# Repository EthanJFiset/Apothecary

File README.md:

# Apothecary
Apothocary is an STM32H7-based USB audio interface and DSP board designed for prototyping real-time guitar effects. Features include a robust STM32H7 MCU complete with external SDRAM and QPSI flash memory, 24-bit 144-dB stereo codec, USB 2.0 connectivity and expansion ports for an external stomp box.

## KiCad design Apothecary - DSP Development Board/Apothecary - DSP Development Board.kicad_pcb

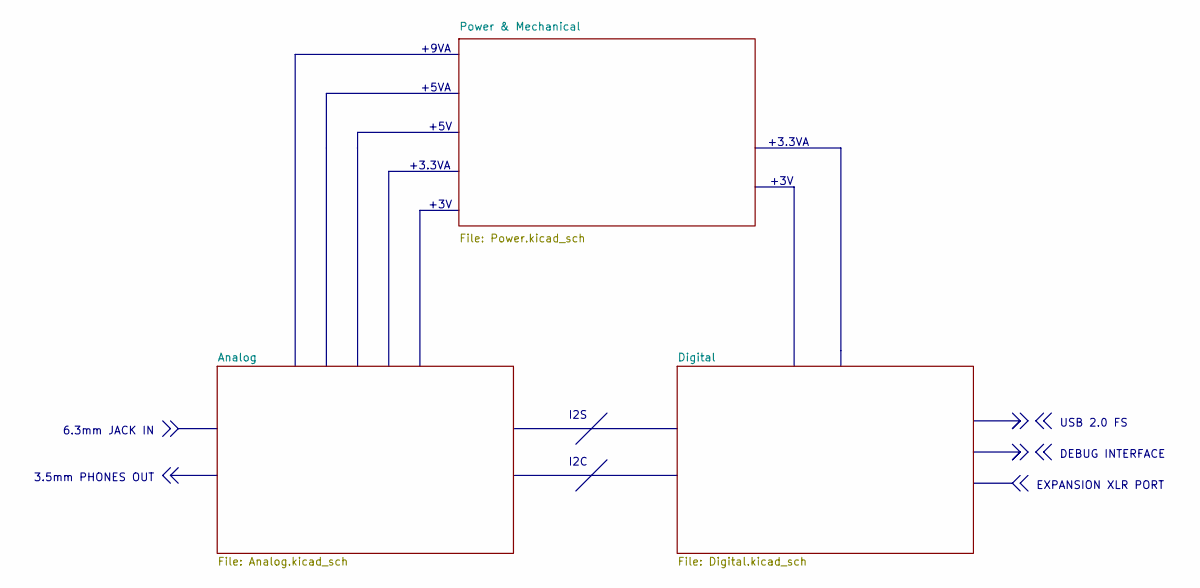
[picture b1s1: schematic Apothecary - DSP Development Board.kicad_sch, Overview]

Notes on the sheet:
+9VA
+3V
EXPANSION XLR PORT
6.3mm JACK IN
DEBUG INTERFACE
USB 2.0 FS
+5V
I2C
+3.3VA
3.5mm PHONES OUT
+5VA
I2S

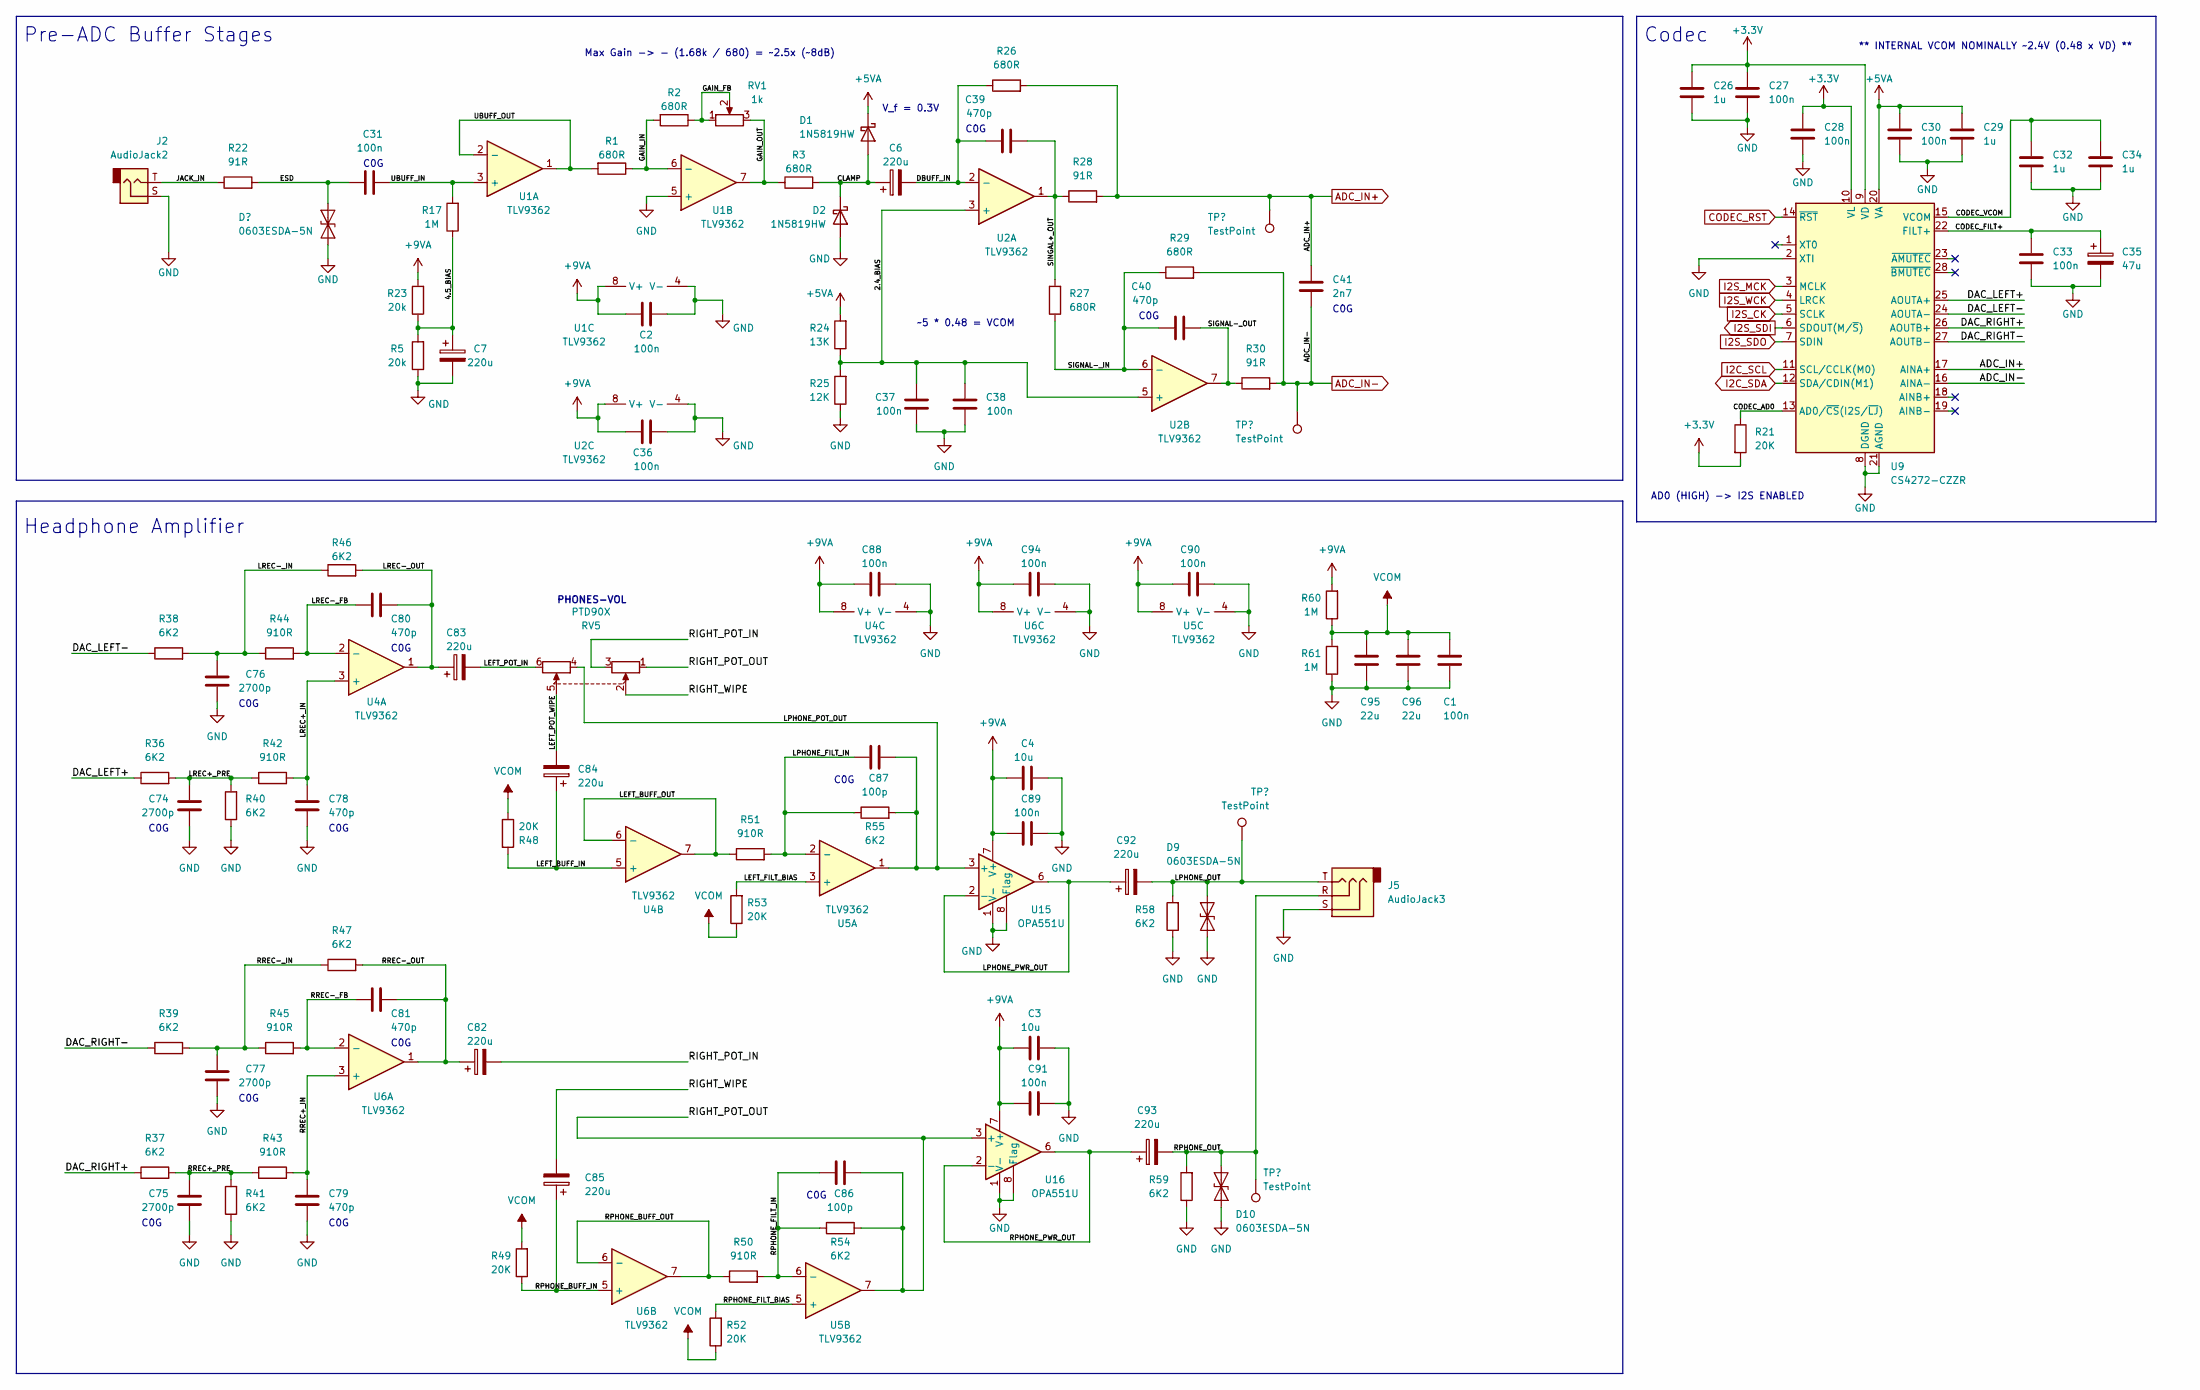
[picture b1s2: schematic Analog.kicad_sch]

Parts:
C1, C2, C27, C28, C30, C31, C33, C36, C37, C38, C88, C89, C90, C91, C94: 100n; C_0402_1005Metric
C3, C4: 10u; C_0805_2012Metric
C6, C7, C82, C83, C84, C85, C92, C93: 220u; CP_Elec_6.3x7.7
C26, C29, C32, C34: 1u; C_0402_1005Metric
C35: 47u; CP_Elec_6.3x7.7
C39, C40, C78, C79, C80, C81: 470p; C_0402_1005Metric
C41: 2n7; C_0603_1608Metric
C74, C75, C76, C77: 2700p; C_0603_1608Metric
C86, C87: 100p; C_0402_1005Metric
C95, C96: 22u; C_1210_3225Metric
D1, D2: 1N5819HW; D_SOD-123
D8, D9, D10: 0603ESDA-5N; D_0603_1608Metric
J2: AudioJack2; Jack_6.35mm_Neutrik_NMJ4HCD2_Horizontal
J5: AudioJack3; Jack_3.5mm_CUI_SJ1-3533NG_Horizontal
R1, R2, R3, R26, R27, R29: 680R; R_0603_1608Metric
R5, R23: 20k; R_0603_1608Metric
R17, R60, R61: 1M; R_0805_2012Metric
R21, R48, R49, R52, R53: 20K; R_0603_1608Metric
R22, R28, R30: 91R; R_0603_1608Metric
R24: 13K; R_0603_1608Metric
R25: 12K; R_0603_1608Metric
R36, R37, R38, R39, R40, R41, R46, R47, R54, R55, R58, R59: 6K2; R_0603_1608Metric
R42, R43, R44, R45, R50, R51: 910R; R_0603_1608Metric
RV1: 1k; Potentiometer_Bourns_PTV09A-2_Single_Horizontal
RV5: PTD90X; PTD-902
TP11, TP12, TP13, TP14: TestPoint; TestPoint_Pad_D1.0mm
U1, U2, U4, U5, U6: TLV9362; SOIC-8-1EP_3.9x4.9mm_P1.27mm_EP2.41x3.81mm
U9: CS4272-CZZR; TSSOP-28_4.4x9.7mm_P0.65mm
U15, U16: OPA551U; SOIC-8_3.9x4.9mm_P1.27mm

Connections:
+3.3V: C26.1, C27.1, C28.1, R21.2, U9.9 (VD), U9.10 (VL); also elsewhere on the board
+5VA: C29.1, C30.1, D1.1 (K), R24.2, U9.20 (VA); also elsewhere on the board
+9VA: C2.1, C3.2, C4.2, C36.1, C88.2, C89.2, C90.2, C91.2, C94.2, R23.2, R60.2, U1.8 (V+), U2.8 (V+), U4.8 (V+), U5.8 (V+), U6.8 (V+), U15.7 (V+), U16.7 (V+); also elsewhere on the board
/Analog/2.4_BIAS: C37.2, C38.2, R24.1, R25.2, U2.3 (+), U2.5 (+)
/Analog/4.5_BIAS: C7.1, R5.2, R17.1, R23.1
/Analog/CLAMP: C6.1, D1.2 (A), D2.1 (K), R3.2
/Analog/CODEC_AD0: R21.1, U9.13 (AD0/~CS(I2S/~LJ))
/Analog/CODEC_FILT+: C33.1, C35.1, U9.22 (FILT+)
/Analog/CODEC_VCOM: C32.1, C34.1, U9.15 (VCOM)
/Analog/DAC_LEFT+: R36.1, U9.25 (AOUTA+)
/Analog/DAC_LEFT-: R38.1, U9.24 (AOUTA-)
/Analog/DAC_RIGHT+: R37.1, U9.26 (AOUTB+)
/Analog/DAC_RIGHT-: R39.1, U9.27 (AOUTB-)
/Analog/DBUFF_IN: C6.2, C39.1, R26.1, U2.2 (-)
/Analog/ESD: C31.1, D8.2 (A2), R22.2
/Analog/GAIN_FB: R2.1, RV1.1, RV1.2
/Analog/GAIN_IN: R1.1, R2.2, U1.6 (-)
/Analog/GAIN_OUT: R3.1, RV1.3, U1.7
/Analog/JACK_IN: J2.T, R22.1
/Analog/LEFT_BUFF_IN: C84.1, R48.2, U4.5 (+)
/Analog/LEFT_BUFF_OUT: R51.1, U4.6 (-), U4.7
/Analog/LEFT_FILT_BIAS: R53.2, U5.3 (+)
/Analog/LEFT_POT_IN: C83.2, RV5.6
/Analog/LEFT_POT_WIPE: C84.2, RV5.5
/Analog/LPHONE_FILT_IN: C87.2, R51.2, R55.1, U5.2 (-)
/Analog/LPHONE_OUT: C92.2, D9.2 (A2), J5.T, R58.2, TP13.1
/Analog/LPHONE_POT_OUT: C87.1, R55.2, RV5.4, U5.1, U15.3 (+)
/Analog/LPHONE_PWR_OUT: C92.1, U15.2 (-), U15.6
/Analog/LREC+_IN: C78.1, R42.2, U4.3 (+)
/Analog/LREC+_PRE: C74.1, R36.2, R40.2, R42.1
/Analog/LREC-_FB: C80.2, R44.2, U4.2 (-)
/Analog/LREC-_IN: C76.1, R38.2, R44.1, R46.1
/Analog/LREC-_OUT: C80.1, C83.1, R46.2, U4.1
/Analog/RIGHT_POT_IN: C82.2, RV5.3
/Analog/RIGHT_POT_OUT: C86.1, R54.2, RV5.1, U5.7, U16.3 (+)
/Analog/RIGHT_WIPE: C85.2, RV5.2
/Analog/RPHONE_BUFF_IN: C85.1, R49.1, U6.5 (+)
/Analog/RPHONE_BUFF_OUT: R50.1, U6.6 (-), U6.7
/Analog/RPHONE_FILT_BIAS: R52.2, U5.5 (+)
/Analog/RPHONE_FILT_IN: C86.2, R50.2, R54.1, U5.6 (-)
/Analog/RPHONE_OUT: C93.2, D10.2 (A2), J5.R, R59.2, TP14.1
/Analog/RPHONE_PWR_OUT: C93.1, U16.2 (-), U16.6
/Analog/RREC+_IN: C79.1, R43.2, U6.3 (+)
/Analog/RREC+_PRE: C75.1, R37.2, R41.2, R43.1
/Analog/RREC-_FB: C81.2, R45.2, U6.2 (-)
/Analog/RREC-_IN: C77.1, R39.2, R45.1, R47.1
/Analog/RREC-_OUT: C81.1, C82.1, R47.2, U6.1
/Analog/SIGNAL-_IN: C40.1, R27.1, R29.1, U2.6 (-)
/Analog/SIGNAL-_OUT: C40.2, R30.1, U2.7
/Analog/SINGAL+_OUT: C39.2, R27.2, R28.1, U2.1
/Analog/UBUFF_IN: C31.2, R17.2, U1.3 (+)
/Analog/UBUFF_OUT: R1.2, U1.1, U1.2 (-)
ADC_IN+: C41.1, R26.2, R28.2, TP12.1, U9.17 (AINA+)
ADC_IN-: C41.2, R29.2, R30.2, TP11.1, U9.16 (AINA-)
CODEC_RST: U9.14 (~RST); also elsewhere on the board
GND: C1.2, C2.2, C3.1, C4.1, C7.2, C26.2, C27.2, C28.2, C29.2, C30.2, C32.2, C33.2, C34.2, C35.2, C36.2, C37.1, C38.1, C74.2, C75.2, C76.2, C77.2, C78.2, C79.2, C88.1, C89.1, C90.1, C91.1, C94.1, C95.2, C96.2, D2.2 (A), D8.1 (A1), D9.1 (A1), D10.1 (A1), J2.S, J5.S, R5.1, R25.1, R40.1, R41.1, R58.1, R59.1, R61.1, U1.4 (V-), U1.5 (+), U2.4 (V-), U4.4 (V-), U5.4 (V-), U6.4 (V-), U9.2 (XTI), U9.8 (DGND), U9.21 (AGND), U15.1 (V-), U15.4 (V-), U15.5 (V-), U15.8 (Flag), U16.1 (V-), U16.4 (V-), U16.5 (V-), U16.8 (Flag); also elsewhere on the board
I2C_SCL: U9.11 (SCL/CCLK(M0)); also elsewhere on the board
I2C_SDA: U9.12 (SDA/CDIN(M1)); also elsewhere on the board
I2S_CK: U9.5 (SCLK); also elsewhere on the board
I2S_MCK: U9.3 (MCLK); also elsewhere on the board
I2S_SDI: U9.6 (SDOUT(M/~S)); also elsewhere on the board
I2S_SDO: U9.7 (SDIN); also elsewhere on the board
I2S_WCK: U9.4 (LRCK); also elsewhere on the board
VCOM: C1.1, C95.1, C96.1, R48.1, R49.2, R52.1, R53.1, R60.1, R61.2

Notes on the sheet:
C0G
Pre-ADC Buffer Stages
** INTERNAL VCOM NOMINALLY ~2.4V (0.48 x VD) **
Headphone Amplifier
V_f = 0.3V
PHONES-VOL
Codec
~5 * 0.48 = VCOM
AD0 (HIGH) -> I2S ENABLED
Max Gain -> - (1.68k / 680) = ~2.5x (~8dB)

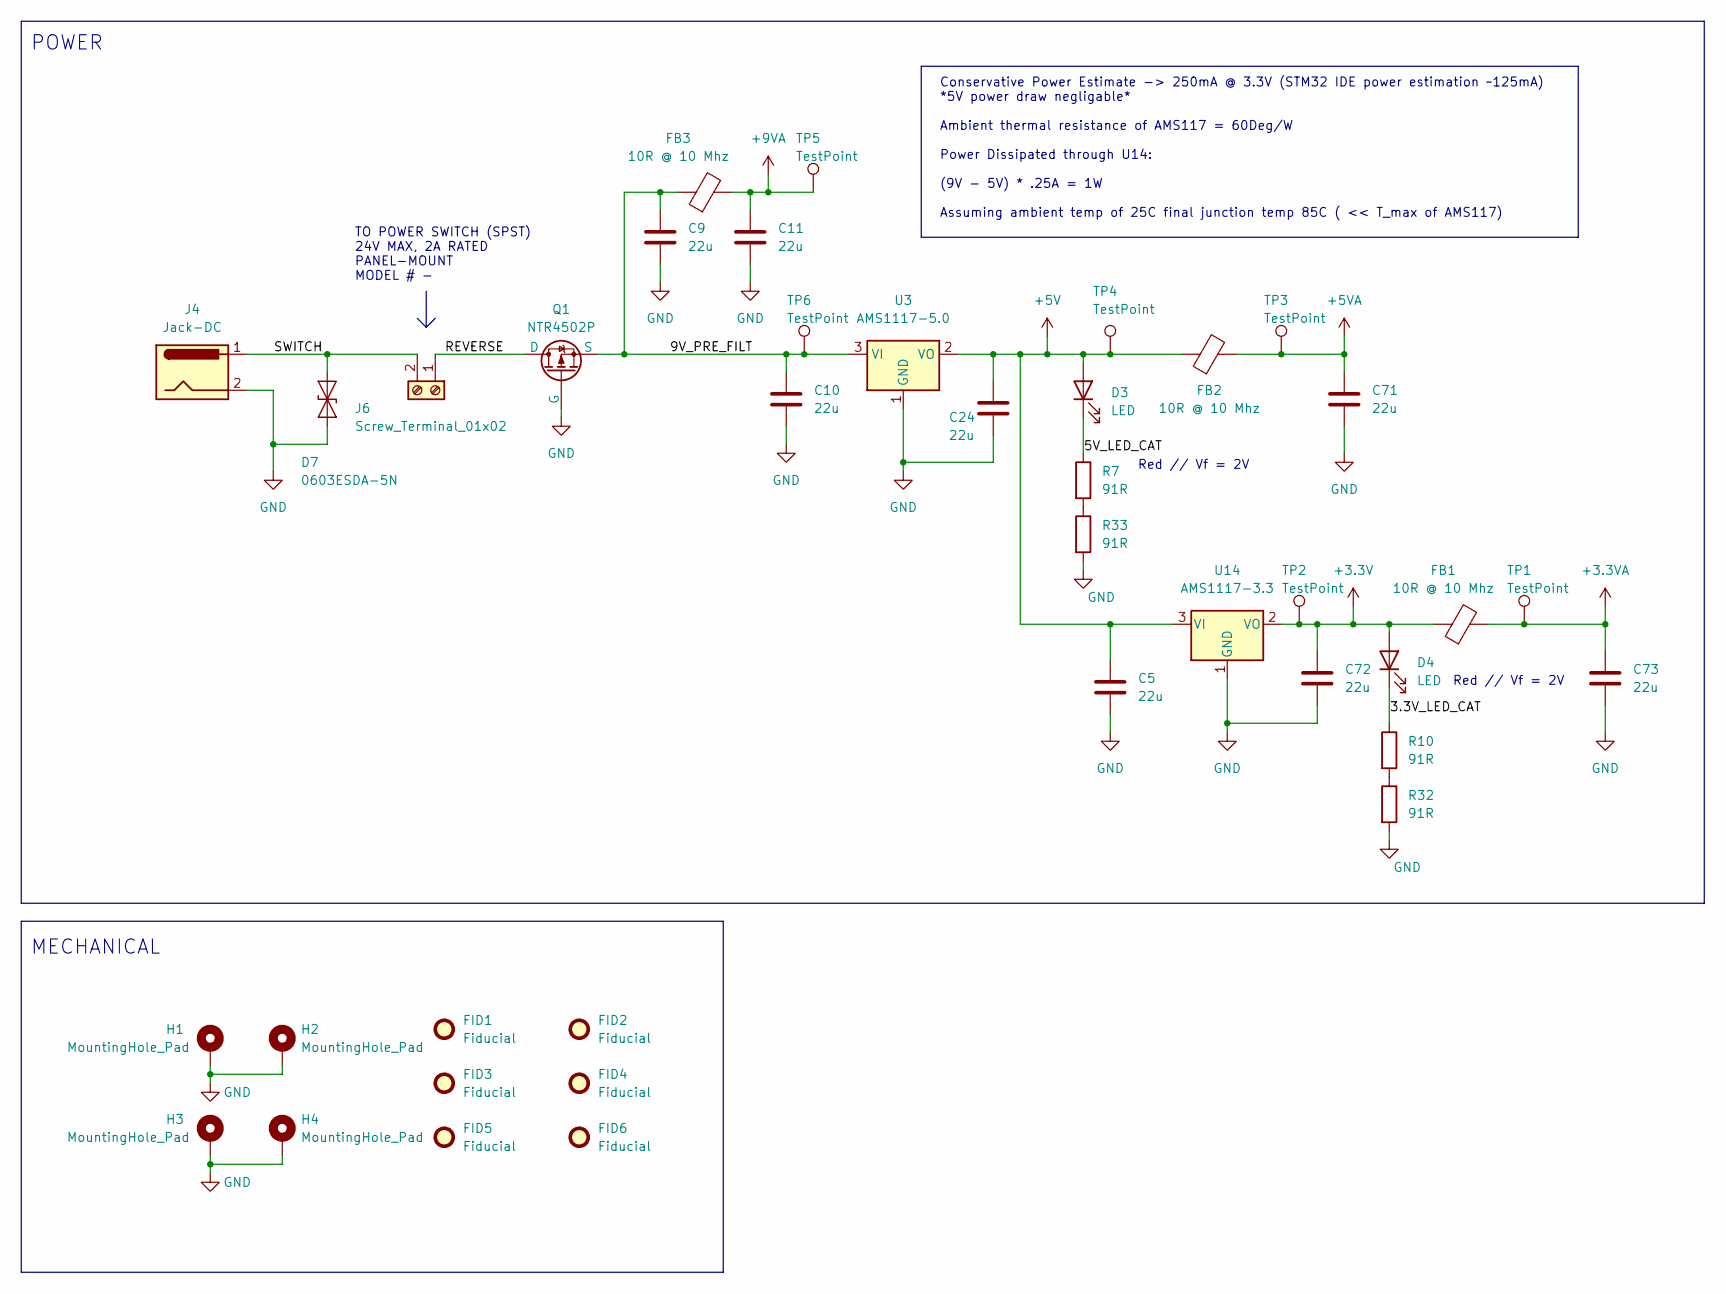
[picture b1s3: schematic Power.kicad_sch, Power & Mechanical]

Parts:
C5, C9, C10, C11, C24, C71, C72, C73: 22u; C_1210_3225Metric
D3, D4: LED; LED_0603_1608Metric
D7: 0603ESDA-5N; D_0603_1608Metric
FB1, FB2, FB3: 10R @ 10 Mhz; L_0805_2012Metric
FID1, FID2, FID3, FID4, FID5, FID6: Fiducial; Fiducial_0.5mm_Mask1mm
H1, H2, H3, H4: MountingHole_Pad; MountingHole_2.7mm_M2.5_DIN965_Pad
J4: Jack-DC; BarrelJack_CUI_PJ-063AH_Horizontal
J6: Screw_Terminal_01x02; TerminalBlock_Phoenix_MKDS-1,5-2_1x02_P5.00mm_Horizontal
Q1: NTR4502P; SOT-23
R7, R10, R32, R33: 91R; R_0603_1608Metric
TP1, TP2, TP3, TP4, TP5, TP6: TestPoint; TestPoint_Pad_D1.5mm
U3: AMS1117-5.0; SOT-223-3_TabPin2
U14: AMS1117-3.3; SOT-223-3_TabPin2

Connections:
+3.3V: C72.2, D4.2 (A), FB1.1, TP2.1, U14.2 (VO); also elsewhere on the board
+3.3VA: C73.2, FB1.2, TP1.1; also elsewhere on the board
+5V: C5.2, C24.2, D3.2 (A), FB2.1, TP4.1, U3.2 (VO), U14.3 (VI)
+5VA: C71.2, FB2.2, TP3.1; also elsewhere on the board
+9VA: C11.2, FB3.2, TP5.1; also elsewhere on the board
/Power & Mechanical/3.3V_LED_CAT: D4.1 (K), R10.1
/Power & Mechanical/5V_LED_CAT: D3.1 (K), R7.1
/Power & Mechanical/9V_PRE_FILT: C9.2, C10.2, FB3.1, Q1.3 (S), TP6.1, U3.3 (VI)
/Power & Mechanical/REVERSE: J6.1, Q1.1 (D)
/Power & Mechanical/SWITCH: D7.2 (A2), J4.1, J6.2
GND: C5.1, C9.1, C10.1, C11.1, C24.1, C71.1, C72.1, C73.1, D7.1 (A1), H1.1, H2.1, H3.1, H4.1, J4.2, Q1.2 (G), R32.2, R33.2, U3.1 (GND), U14.1 (GND); also elsewhere on the board
unnamed: R10.2, R32.1
unnamed: R7.2, R33.1

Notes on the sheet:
Conservative Power Estimate -> 250mA @ 3.3V (STM32 IDE power estimation ~125mA) *5V power draw negligable* Ambient thermal resistance of AMS117 = 60Deg/W Power Dissipated through U14: (9V - 5V) * .25A = 1W Assuming ambient temp of 25C final junction temp 85C ( << T_max of AMS117)
TO POWER SWITCH (SPST) 24V MAX, 2A RATED PANEL-MOUNT MODEL # -
MECHANICAL
POWER
Red // Vf = 2V

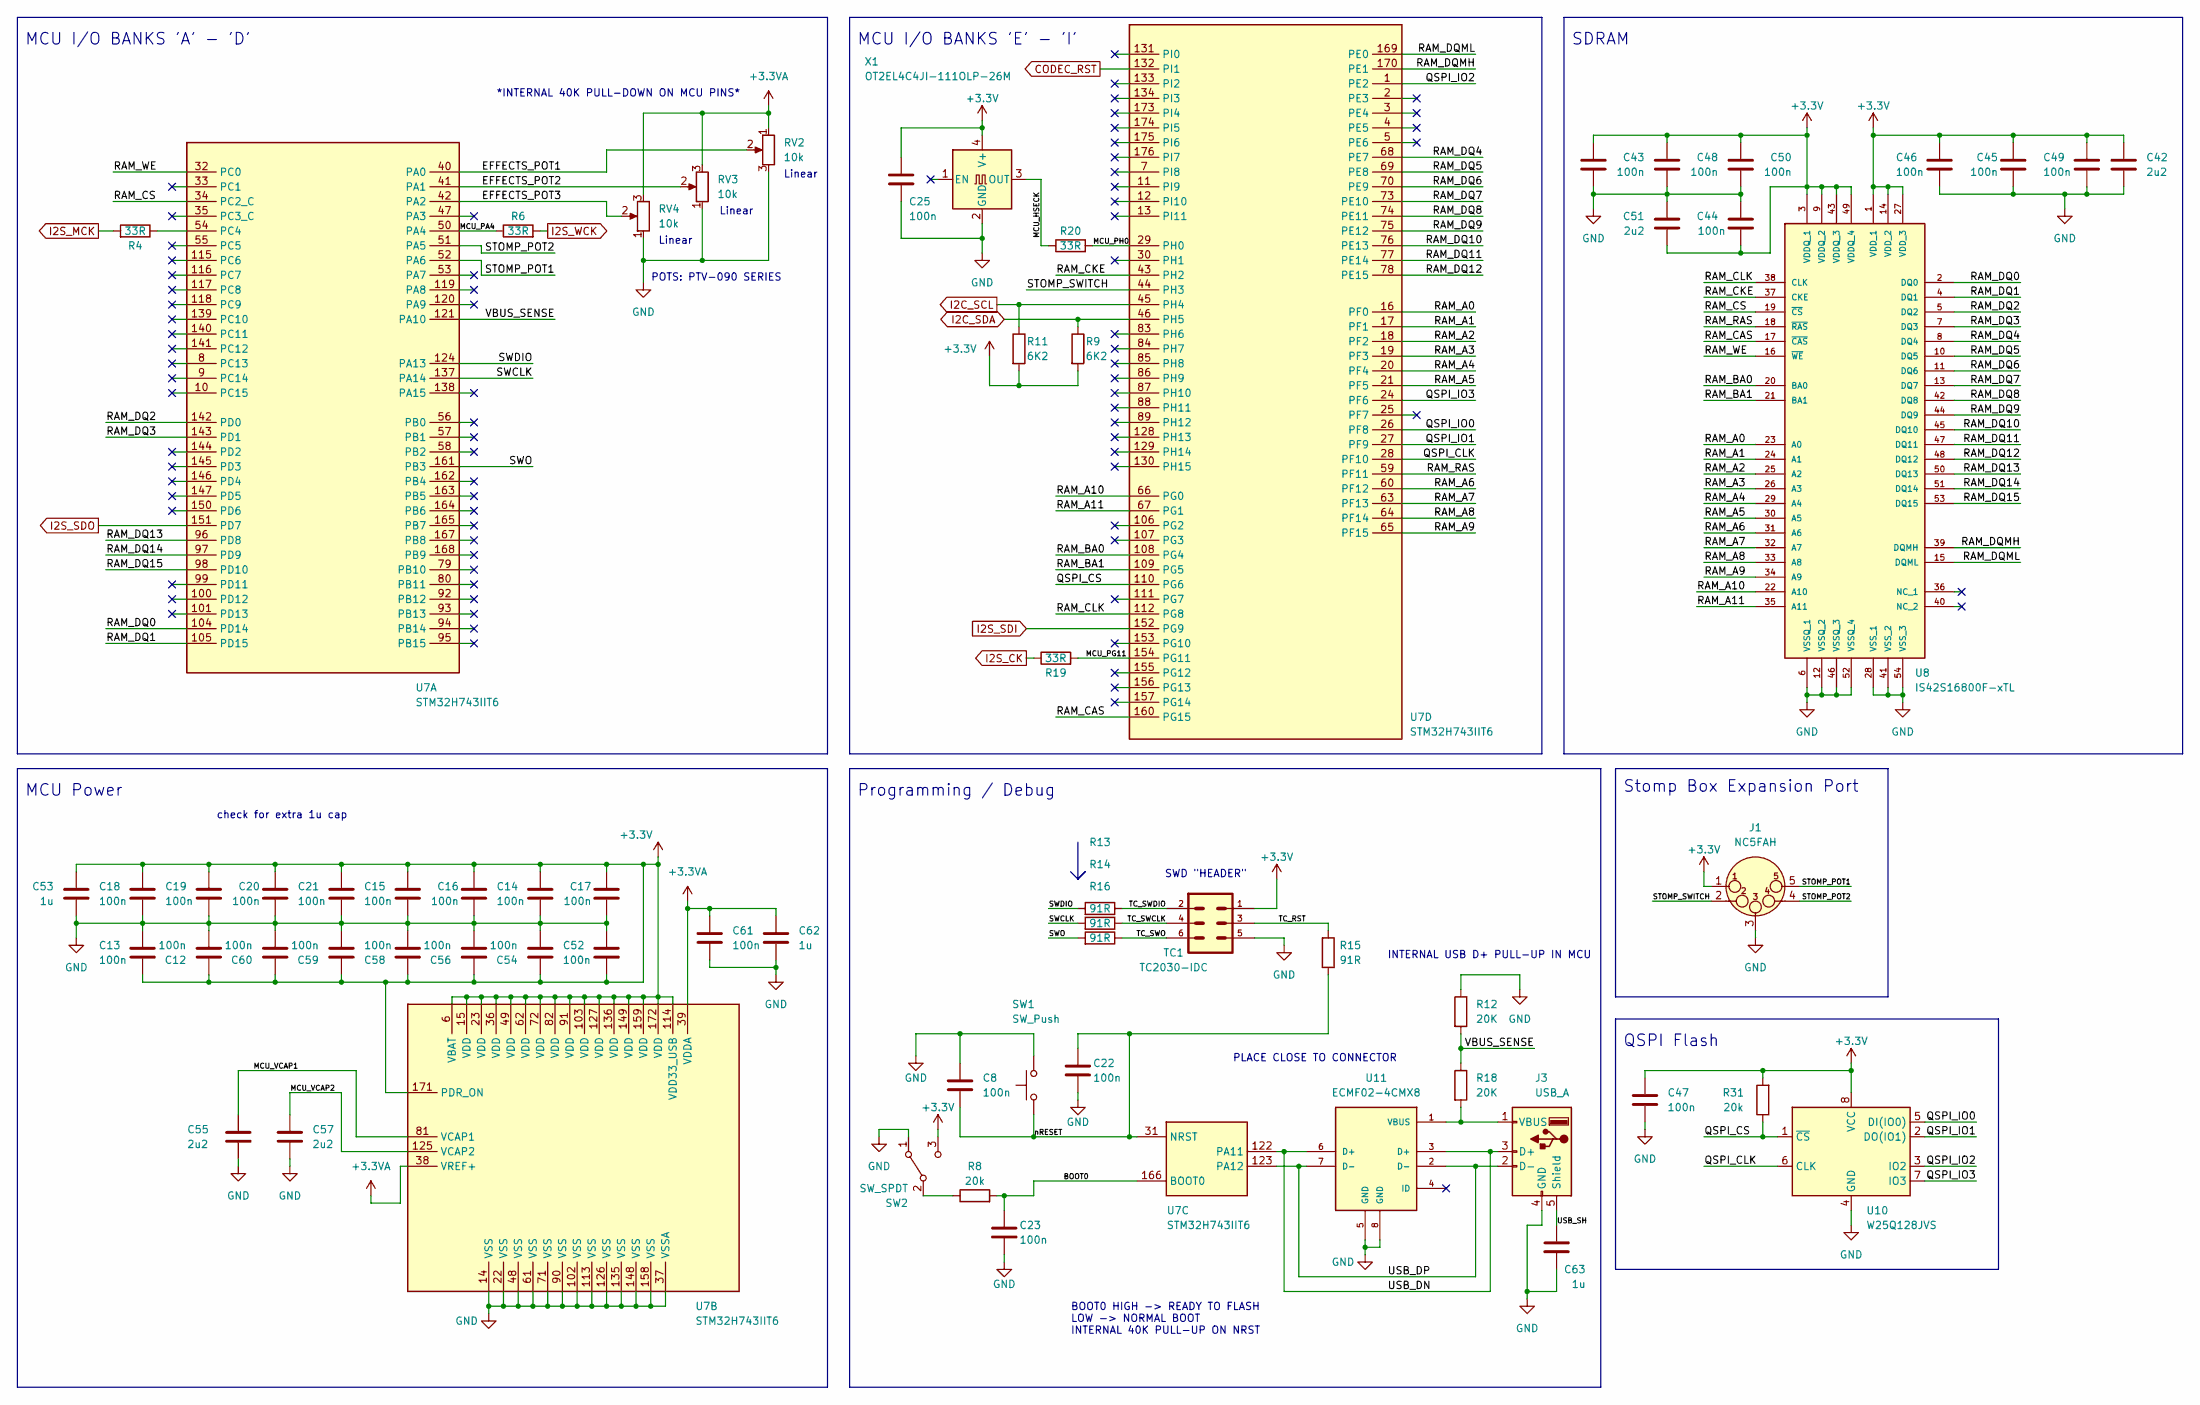
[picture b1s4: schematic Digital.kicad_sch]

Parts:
C8, C12, C13, C14, C15, C16, C17, C18, C19, C20, C21, C22, C23, C25, C43, C44, C45, C46, C47, C48, C49, C50, C52, C54, C56, C58, C59, C60, C61: 100n; C_0402_1005Metric
C42, C51, C55, C57: 2u2; C_0805_2012Metric
C53, C62, C63: 1u; C_0402_1005Metric
J1: NC5FAH; Jack_XLR_Neutrik_NC5FAH_Horizontal
J3: USB_A; MOLEX_0480372200
R4, R6, R19, R20: 33R; R_0603_1608Metric
R8, R31: 20k; R_0603_1608Metric
R9, R11: 6K2; R_0603_1608Metric
R12, R18: 20K; R_0603_1608Metric
R13, R14, R15, R16: 91R; R_0603_1608Metric
RV2, RV3, RV4: 10k; Potentiometer_Bourns_PTV09A-2_Single_Horizontal
SW1: SW_Push; Pushbutton_CUI_TS04
SW2: SW_SPDT; SW_E-Switch_EG1224_SPDT_Angled
TC1: TC2030-IDC; Tag-Connect_TC2030-IDC-FP_2x03_P1.27mm_Vertical
U7: STM32H743IIT6; LQFP-176_24x24mm_P0.5mm
U8: IS42S16800F-xTL; TSOP-II-54_22.2x10.16mm_P0.8mm; MOUSER_PART_NUMBER 870-IS42S16800F-7TL
U10: W25Q128JVS; SOIC-8_5.23x5.23mm_P1.27mm
U11: ECMF02-4CMX8; FIL_ECMF02-4CMX8; PARTREV 3
X1: OT2EL4C4JI-111OLP-26M; Crystal_SMD_3225-4Pin_3.2x2.5mm

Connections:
+3.3V: C12.1, C13.1, C14.2, C15.2, C16.2, C17.2, C18.2, C19.2, C20.2, C21.2, C25.1, C42.2, C43.2, C44.1, C45.2, C46.2, C47.1, C48.2, C49.2, C50.2, C51.1, C52.1, C53.2, C54.1, C56.1, C58.1, C59.1, C60.1, J1.1, R9.2, R11.2, R31.2, SW2.3 (C), TC1.1, U7.6 (VBAT), U7.15 (VDD), U7.23 (VDD), U7.36 (VDD), U7.49 (VDD), U7.62 (VDD), U7.72 (VDD), U7.82 (VDD), U7.91 (VDD), U7.103 (VDD), U7.114 (VDD33_USB), U7.127 (VDD), U7.136 (VDD), U7.149 (VDD), U7.159 (VDD), U7.171 (PDR_ON), U7.172 (VDD), U8.1 (VDD_1), U8.3 (VDDQ_1), U8.9 (VDDQ_2), U8.14 (VDD_2), U8.27 (VDD_3), U8.43 (VDDQ_3), U8.49 (VDDQ_4), U10.8 (VCC), X1.4 (V+); also elsewhere on the board
+3.3VA: C61.1, C62.1, RV2.1, RV3.3, RV4.3, U7.38 (VREF+), U7.39 (VDDA); also elsewhere on the board
/Digital/BOOT0: C23.1, R8.2, U7.166 (BOOT0)
/Digital/EFFECTS_POT1: RV2.2, U7.40 (PA0)
/Digital/EFFECTS_POT2: RV3.2, U7.41 (PA1)
/Digital/EFFECTS_POT3: RV4.2, U7.42 (PA2)
/Digital/MCU_HSECK: R20.1, X1.3 (OUT)
/Digital/MCU_PA4: R6.1, U7.50 (PA4)
/Digital/MCU_PG11: R19.2, U7.154 (PG11)
/Digital/MCU_PH0: R20.2, U7.29 (PH0)
/Digital/MCU_VCAP1: C55.1, U7.81 (VCAP1)
/Digital/MCU_VCAP2: C57.1, U7.125 (VCAP2)
/Digital/QSPI_CLK: U7.28 (PF10), U10.6 (CLK)
/Digital/QSPI_CS: R31.1, U7.110 (PG6), U10.1 (~CS)
/Digital/QSPI_IO0: U7.26 (PF8), U10.5 (DI(IO0))
/Digital/QSPI_IO1: U7.27 (PF9), U10.2 (DO(IO1))
/Digital/QSPI_IO2: U7.1 (PE2), U10.3 (IO2)
/Digital/QSPI_IO3: U7.24 (PF6), U10.7 (IO3)
/Digital/RAM_A0: U7.16 (PF0), U8.23 (A0)
/Digital/RAM_A1: U7.17 (PF1), U8.24 (A1)
/Digital/RAM_A2: U7.18 (PF2), U8.25 (A2)
/Digital/RAM_A3: U7.19 (PF3), U8.26 (A3)
/Digital/RAM_A4: U7.20 (PF4), U8.29 (A4)
/Digital/RAM_A5: U7.21 (PF5), U8.30 (A5)
/Digital/RAM_A6: U7.60 (PF12), U8.31 (A6)
/Digital/RAM_A7: U7.63 (PF13), U8.32 (A7)
/Digital/RAM_A8: U7.64 (PF14), U8.33 (A8)
/Digital/RAM_A9: U7.65 (PF15), U8.34 (A9)
/Digital/RAM_A10: U7.66 (PG0), U8.22 (A10)
/Digital/RAM_A11: U7.67 (PG1), U8.35 (A11)
/Digital/RAM_BA0: U7.108 (PG4), U8.20 (BA0)
/Digital/RAM_BA1: U7.109 (PG5), U8.21 (BA1)
/Digital/RAM_CAS: U7.160 (PG15), U8.17 (~CAS)
/Digital/RAM_CKE: U7.43 (PH2), U8.37 (CKE)
/Digital/RAM_CLK: U7.112 (PG8), U8.38 (CLK)
/Digital/RAM_CS: U7.34 (PC2_C), U8.19 (~CS)
/Digital/RAM_DQ0: U7.104 (PD14), U8.2 (DQ0)
/Digital/RAM_DQ1: U7.105 (PD15), U8.4 (DQ1)
/Digital/RAM_DQ2: U7.142 (PD0), U8.5 (DQ2)
/Digital/RAM_DQ3: U7.143 (PD1), U8.7 (DQ3)
/Digital/RAM_DQ4: U7.68 (PE7), U8.8 (DQ4)
/Digital/RAM_DQ5: U7.69 (PE8), U8.10 (DQ5)
/Digital/RAM_DQ6: U7.70 (PE9), U8.11 (DQ6)
/Digital/RAM_DQ7: U7.73 (PE10), U8.13 (DQ7)
/Digital/RAM_DQ8: U7.74 (PE11), U8.42 (DQ8)
/Digital/RAM_DQ9: U7.75 (PE12), U8.44 (DQ9)
/Digital/RAM_DQ10: U7.76 (PE13), U8.45 (DQ10)
/Digital/RAM_DQ11: U7.77 (PE14), U8.47 (DQ11)
/Digital/RAM_DQ12: U7.78 (PE15), U8.48 (DQ12)
/Digital/RAM_DQ13: U7.96 (PD8), U8.50 (DQ13)
/Digital/RAM_DQ14: U7.97 (PD9), U8.51 (DQ14)
/Digital/RAM_DQ15: U7.98 (PD10), U8.53 (DQ15)
/Digital/RAM_DQMH: U7.170 (PE1), U8.39 (DQMH)
/Digital/RAM_DQML: U7.169 (PE0), U8.15 (DQML)
/Digital/RAM_RAS: U7.59 (PF11), U8.18 (~RAS)
/Digital/RAM_WE: U7.32 (PC0), U8.16 (~WE)
/Digital/STOMP_POT1: J1.5, U7.52 (PA6)
/Digital/STOMP_POT2: J1.4 (P3), U7.51 (PA5)
/Digital/STOMP_SWITCH: J1.2, U7.44 (PH3)
/Digital/SWCLK: R14.2, U7.137 (PA14)
/Digital/SWDIO: R13.2, U7.124 (PA13)
/Digital/SWO: R16.2, U7.161 (PB3)
/Digital/TC_RST: R15.2, TC1.3
/Digital/TC_SWCLK: R14.1, TC1.4
/Digital/TC_SWDIO: R13.1, TC1.2
/Digital/TC_SWO: R16.1, TC1.6
/Digital/USB_DN: J3.3 (D+), U7.122 (PA11), U11.3 (D+), U11.6 (D+)
/Digital/USB_DP: J3.2 (D-), U7.123 (PA12), U11.2 (D-), U11.7 (D-)
/Digital/USB_SH: C63.1, J3.5 (Shield)
/Digital/VBUS_SENSE: R12.2, R18.1, U7.121 (PA10)
/Digital/nRESET: C8.2, C22.1, R15.1, SW1.1, U7.31 (NRST)
CODEC_RST: U7.132 (PI1); also elsewhere on the board
GND: C8.1, C12.2, C13.2, C14.1, C15.1, C16.1, C17.1, C18.1, C19.1, C20.1, C21.1, C22.2, C23.2, C25.2, C42.1, C43.1, C44.2, C45.1, C46.1, C47.2, C48.1, C49.1, C50.1, C51.2, C52.2, C53.1, C54.2, C55.2, C56.2, C57.2, C58.2, C59.2, C60.2, C61.2, C62.2, C63.2, J1.3, J3.4 (GND), R12.1, RV2.3, RV3.1, RV4.1, SW1.2, SW2.1 (A), TC1.5, U7.14 (VSS), U7.22 (VSS), U7.37 (VSSA), U7.48 (VSS), U7.61 (VSS), U7.71 (VSS), U7.90 (VSS), U7.102 (VSS), U7.113 (VSS), U7.126 (VSS), U7.135 (VSS), U7.148 (VSS), U7.158 (VSS), U8.6 (VSSQ_1), U8.12 (VSSQ_2), U8.28 (VSS_1), U8.41 (VSS_2), U8.46 (VSSQ_3), U8.52 (VSSQ_4), U8.54 (VSS_3), U10.4 (GND), U11.5 (GND), U11.8 (GND), X1.2 (GND); also elsewhere on the board
I2C_SCL: R11.1, U7.45 (PH4); also elsewhere on the board
I2C_SDA: R9.1, U7.46 (PH5); also elsewhere on the board
I2S_CK: R19.1; also elsewhere on the board
I2S_MCK: R4.2; also elsewhere on the board
I2S_SDI: U7.152 (PG9); also elsewhere on the board
I2S_SDO: U7.151 (PD7); also elsewhere on the board
I2S_WCK: R6.2; also elsewhere on the board
unnamed: J3.1 (VBUS), R18.2, U11.1 (VBUS)
unnamed: R8.1, SW2.2 (B)
unnamed: R4.1, U7.54 (PC4)

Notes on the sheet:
*INTERNAL 40K PULL-DOWN ON MCU PINS*
Programming / Debug
Linear
PLACE CLOSE TO CONNECTOR
Linear
BOOT0 HIGH -> READY TO FLASH LOW -> NORMAL BOOT INTERNAL 40K PULL-UP ON NRST
SWD "HEADER"
MCU Power
MCU I/O BANKS 'A' - 'D'
INTERNAL USB D+ PULL-UP IN MCU
SDRAM
MCU I/O BANKS 'E' - 'I'
Stomp Box Expansion Port
QSPI Flash
check for extra 1u cap
POTS: PTV-090 SERIES

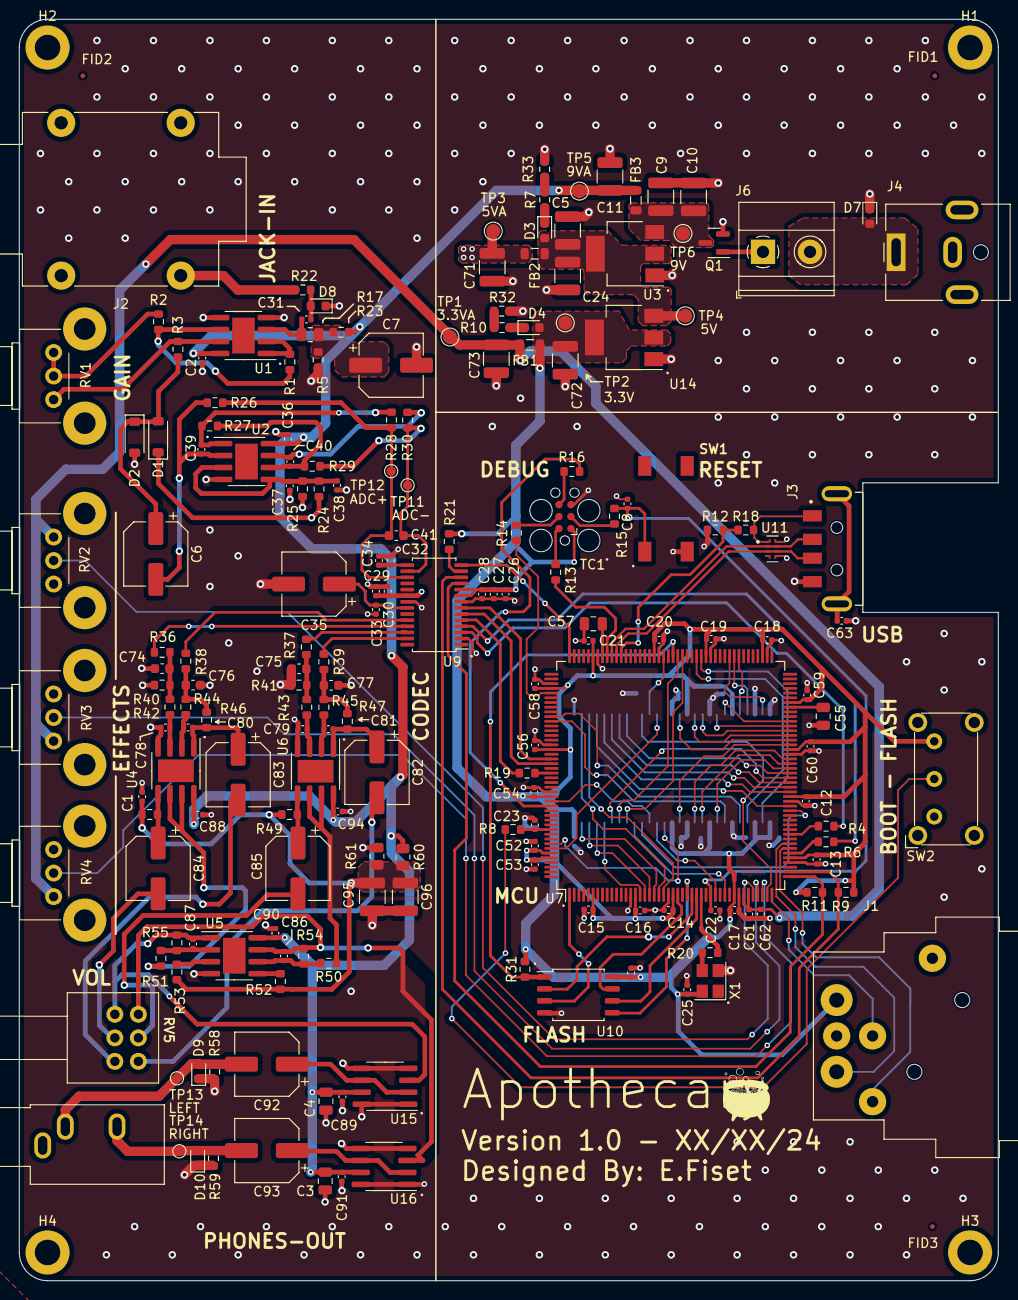
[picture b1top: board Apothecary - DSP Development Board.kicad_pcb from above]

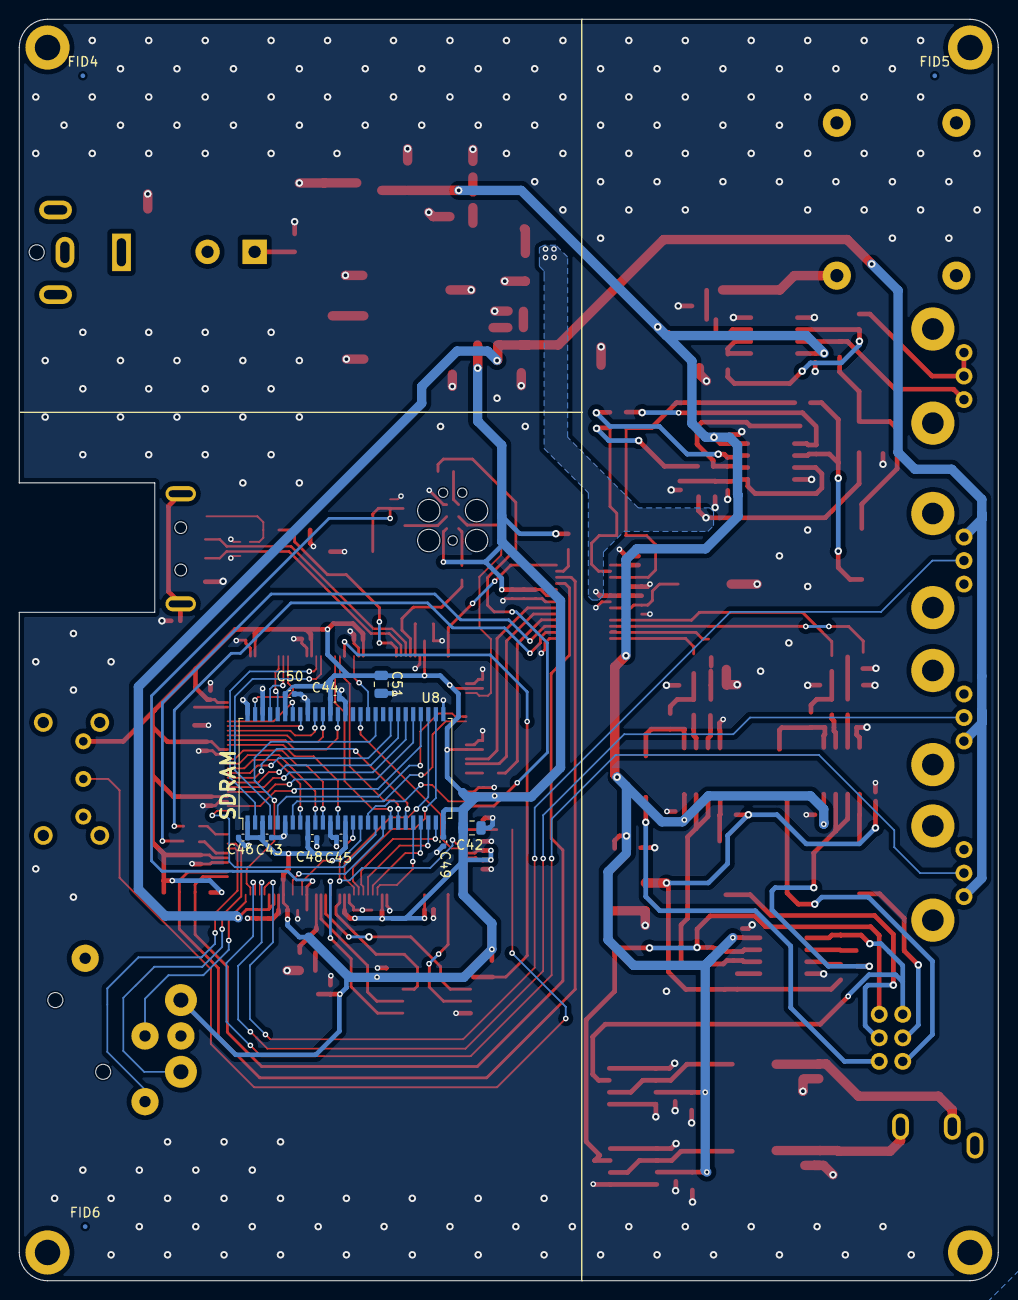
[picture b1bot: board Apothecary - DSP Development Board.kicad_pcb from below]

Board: 4 copper layers, 104.0 x 134.0 mm, 207 parts (13 on the bottom side), 145 nets.

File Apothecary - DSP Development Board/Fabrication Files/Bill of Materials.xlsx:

Date: | 45364.572418981479
Project: | Apothecary DSP Board v1.0
Tool: | Eeschema 7.0.9
Component Count: | 183
Ref | Qnty | Description | Footprint | Mfg. Part # | Mfg. | Type | Notes
C1, C2, C8, C12, C13, C14, C15, C16, C17, C18, C19, C20, C21, C22, C23, C25, C2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 | 44 | 100n CAP CER X7R 25V 10% | 0402 | C0402C104K3R | Kemet | SMD
C3, C4 | 2 | 10u CAP CER X5R 25V 10% | 0805 | C0805C106K3P7210 | Kemet | SMD
C5, C9, C10, C11, C24, C71, C72, C73, C95, C96 | 10 | 22u CAP CER X7R 24V 5% | 1210 | C1210C226K3PAC | Kemet | SMD
C26, C29, C32, C34, C53, C62, C63 | 7 | 1u CAP CER X7R 24V 5% | 0805 | C0805C105J3RECTU | Kemet | SMD
C35 | 1 | 47u CAP AL. ELC 25V 20% | SMD 6.3x6.3x8mm | EEV476M025A9GAA | Kemet | SMD
C39, C40, C78, C79, C80, C81 | 6 | 470p CAP CER C0G 25V 5% | 0402 | C0402C471J3G | Kemet | SMD
C42, C51, C55, C57 | 4 | 2u2 CAP CER X5R 24V 5% | 0805 | C0805C225K3P | Kemet | SMD
C74, C75, C76, C77, C41 | 4 | 2700p CAP CER C0G 25V 5% | 0603 | C0603C272J3G | Kemet | SMD
C6, C7, C82, C83, C84, C85, C92, C93 | 6 | 100u CAP AL. ELC 25V 20% | SMD 6.3x6.3x8mm | EEV227M025S9MAA | Kemet | SMD
C86, C87 | 2 | 100p CAP CER C0G 25V 5% | 0402 | C0402C101J3G | Kemet | SMD
D1, D2 | 2 | Schottky Diode Vf = 0.51 1A SBR 40Vrm | SOD-123 | 1N5819HW | Diodes Inc. | SMD
D3, D4 | 2 | Red LED, Vf = 2V @ 20mA | 0603 | 150060RS75000 | Wurth Elektronik | SMD
D7, D8, D9, D10 | 4 | ESD Diode 30 Vw, 0.15pF, 15kV Vc | 0603 | 0603ESDA-5N | Bussman-Eaton | SMD
FB1, FB2, FB3 | 3 | Ferrite Bead 1000MHz 10Ohm 3000mA AEC-Q200 | 0805 | 742792011 | Wurth Elektronik | SMD
J1 | 1 | 5-Pin Female XLR Jack | NC5FAH | NC5FAH | Neutrik | THT
J2 | 1 | 6.3mm Mono Female Jack | NMJ4HCD2 | NMJ4HCD2 | Neutrik | THT
J3 | 1 | Female USB 2.0 Jack, Middle mount | SMD | 0480372200 | Molex | SMD
J4 | 1 | Female DC Barrel Jack, 8.0A | THT | PJ-063AH | CUI Devices | THT
J5 | 1 | 3-Pin Stereo 3.5mm Phones Jack, Ground Connection | THT | SJ1-3535NG | CUI Devices | THT
J6 | 1 | 01x02 THT Screw Terminal Block | Terminal Block 1x02 P5.00mm | 1729128 | Pheonix Contact | THT
Q1 | 1 | P-Channel Enhancement Mode MOSFET | SOT-23 | NTR4502P | Onsemi | SMD
R1, R2, R3, R10, R26, R27, R29 | 7 | 680R RES OHM 1/10W .5% | 0603 | ERA-3AEB681V | Panasonic | SMD
R4, R6, R19, R20 | 6 | 33R RES OHM 1/10W .5% | 0603 | ERA-3AEB330V | Panasonic | SMD
R5, R8, R23, R31 | 4 | 20k RES OHM 1/10W .5% | 0603 | ERA-3AEB203V | Panasonic | SMD
R7, R42, R43, R44, R45, R50, R51 | 7 | 910R RES OHM 1/10W .5% | 0603 | ERA-3AEB911V | Panasonic | SMD
R9, R11, R36, R37, R38, R39, R40, R41, R46, R47, R54, R55, R58, R59 | 14 | 6K2 RES 1/10W .5% | 0603 | ERA-3AEB622V | Panasonic | SMD
R12, R18, R21, R48, R49, R52, R53 | 7 | 20K RES 1/10W .5% | 0603 | ERA-3AEB203V | Panasonic | SMD
R13, R14, R15, R16, R22, R28, R30, R32, R33 | 7 | 91R RES 1/10W .5% | 0603 | ERA-3AEB910V | Panasonic | SMD
R17, R60, R61 | 3 | 1M RES 1/8W .5% | 0805 | ERA-6AEB105V | Panasonic | SMD
R24 | 1 | 13K RES 1/10W .5% | 0603 | ERA-3AEB133V | Panasonic | SMD
R25 | 1 | 12K RES 1/10W .5% | 0603 | ERA-3AEB123V | Panasonic | SMD
RV1 | 1 | 1K OHM POT 1/10W 20% AUDIO TAPER | THT | PTV09A-2015F-A102 | Bourns | THT
RV2, RV3, RV4 | 3 | 10K OHM POT 1/10W 20% LINEAR TAPER | THT | PTV09A-2015F-B103 | Bourns | THT
RV5 | 1 | 10K OHM POT .025W 20% AUDIO TAPER, DUAL-GANGED | THT | PTD902-2015F-A103 | Bourns | THT
SW1 | 1 | SPST Push-button | SMD | TS04-66-50-BK-100-SMT | CUI Devices | SMD
SW2 | 1 | SPDT Horizontal Mounted Switch | THT | EG1224 | E-Switch | THT
U1, U2, U4, U5, U6 | 5 | Dual Rail-Rail Operational Amplifier | SOIC-8-1EP 3.9x4.9mm P1.27mm EP2.41x3.81mm | TLV9362IDR | Texas Instruments | SMD
U3 | 1 | 1A Low Dropout regulator, positive, 5.0V fixed output, SOT-223 | SOT-223 | AMS1117-5.0 | AMS | SMD
U7 | 1 | ARM Cortex-M7 MCU, 2048KB flash, 864KB RAM, 400MHz, 1.7-3.6V, 140 GPIO, LQFP-176 | LQFP-176 24x24mm P0.5mm | STM32H743IIT6 | ST Microelectronics | SMD
U8 | 1 | 128 Mb SDRAM, 3.3V, Up To 200MHz TSOP-II | TSOP-II-54 22.2x10.16mm P0.8mm | IS42S16800F-xTL | ISSI | SMD
U9 | 1 | 24-Bit, 192 kHz Stereo Audio CODEC, TSSOP-28 | TSSOP-28 4.4x9.7mm P0.65mm | CS4272-CZZR | Cirrus Logic | SMD
U10 | 1 | 128Mb Serial Flash Memory, Standard/Dual/Quad SPI, SOIC-8 | SOIC-8 5.23x5.23mm P1.27mm | W25Q128JVS | Winbond | SMD
U11 | 1 | USB2.0 ESD Array and Common-Mode Choke | SMD | ECMF02-4CMX8 | ST Microelectronics | SMD
U14 | 1 | 1A Low Dropout regulator, positive, 3.3V fixed output, SOT-223 | SOT-223-3 | AMS1117-3.3 | AMS | SMD
U15, U16 | 2 | High-Voltage High-Current Operational Amplifier, bandwidth 3MHz, slew-rate 15V/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 | SOIC-8 3.9x4.9mm P1.27mm | OPA551U | Texas Instruments | SMD
X1 | 1 | Low Power Consumption Clock Oscillator - 26MHz | 3225-4Pin 3.2x2.5mm | OT2EL4C4JI-111OLP-26M | LCSC | SMD

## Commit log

2024-03-23 Add files via upload
    added photo for readme
2024-03-23 Update README.md
    added photo of initial board
